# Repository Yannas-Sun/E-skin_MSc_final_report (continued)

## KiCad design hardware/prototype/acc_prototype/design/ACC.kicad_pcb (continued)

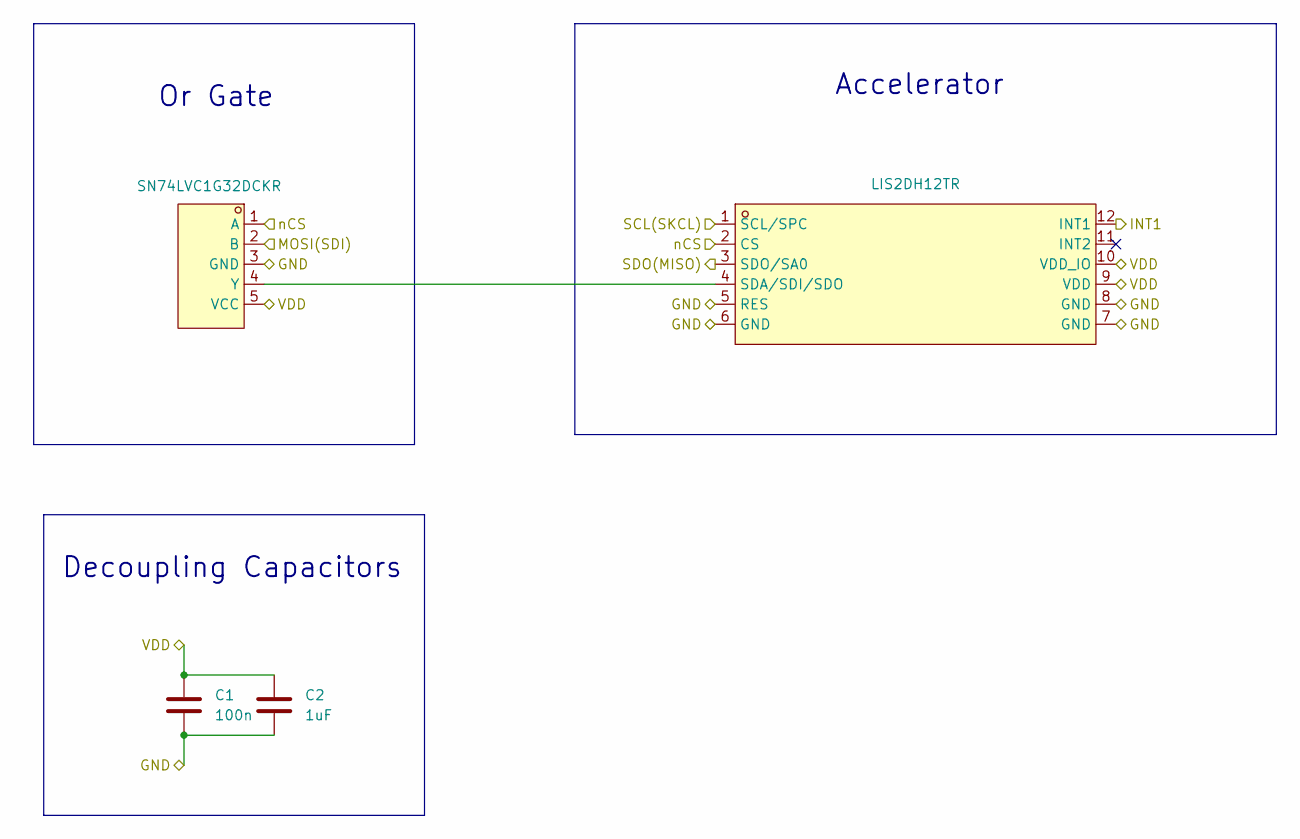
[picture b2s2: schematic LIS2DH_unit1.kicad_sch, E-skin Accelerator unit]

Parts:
C1: 100n; C_0402_1005Metric_Pad0.74x0.62mm_HandSolder; LCSC Part C1525
C2: 1uF; C_0402_1005Metric_Pad0.74x0.62mm_HandSolder; LCSC Part C52923
U1: LIS2DH12TR; LCSC Part C110926
U17: SN74LVC1G32DCKR; LCSC Part C7840

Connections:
/LIS2DH_unit1/INT1: U1.12 (INT1)
GND: C1.2, C2.2, U1.5 (RES), U1.6 (GND), U1.7 (GND), U1.8 (GND), U17.3 (GND); also elsewhere on the board
MISO(SDO): U1.3 (SDO/SA0); also elsewhere on the board
MOSI(SDI): U17.2 (B); also elsewhere on the board
unnamed: U1.4 (SDA/SDI/SDO), U17.4 (Y)
Sclk: U1.1 (SCL/SPC); also elsewhere on the board
VDD: C1.1, C2.1, U1.9 (VDD), U1.10 (VDD_IO), U17.5 (VCC); also elsewhere on the board
nCS_1: U1.2 (CS), U17.1 (A); also elsewhere on the board

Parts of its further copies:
C3, C5, C7, C9, C11, C13, C15, C17: 100n; C_0402_1005Metric_Pad0.74x0.62mm_HandSolder; LCSC Part C1525
C4, C6, C8, C10, C12, C14, C16, C18: 1uF; C_0402_1005Metric_Pad0.74x0.62mm_HandSolder; LCSC Part C52923
U2, U3, U4, U5, U6, U7, U8, U9: LIS2DH12TR; LCSC Part C110926
U18, U19, U20, U21, U22, U23, U24, U25: SN74LVC1G32DCKR; LCSC Part C7840

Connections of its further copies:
/LIS2DH_unit2/INT1: U2.12 (INT1)
/LIS2DH_unit3/INT1: U3.12 (INT1)
/LIS2DH_unit4/INT1: U4.12 (INT1)
/LIS2DH_unit5/INT1: U5.12 (INT1)
/LIS2DH_unit6/INT1: U6.12 (INT1)
/LIS2DH_unit7/INT1: U7.12 (INT1)
/LIS2DH_unit8/INT1: U8.12 (INT1)
/LIS2DH_unit9/INT1: U9.12 (INT1)
GND: C3.2, C4.2, C5.2, C6.2, C7.2, C8.2, C9.2, C10.2, C11.2, C12.2, C13.2, C14.2, C15.2, C16.2, C17.2, C18.2, U2.5 (RES), U2.6 (GND), U2.7 (GND), U2.8 (GND), U3.5 (RES), U3.6 (GND), U3.7 (GND), U3.8 (GND), U4.5 (RES), U4.6 (GND), U4.7 (GND), U4.8 (GND), U5.5 (RES), U5.6 (GND), U5.7 (GND), U5.8 (GND), U6.5 (RES), U6.6 (GND), U6.7 (GND), U6.8 (GND), U7.5 (RES), U7.6 (GND), U7.7 (GND), U7.8 (GND), U8.5 (RES), U8.6 (GND), U8.7 (GND), U8.8 (GND), U9.5 (RES), U9.6 (GND), U9.7 (GND), U9.8 (GND), U18.3 (GND), U19.3 (GND), U20.3 (GND), U21.3 (GND), U22.3 (GND), U23.3 (GND), U24.3 (GND), U25.3 (GND); also elsewhere on the board
MISO(SDO): U2.3 (SDO/SA0), U3.3 (SDO/SA0), U4.3 (SDO/SA0), U5.3 (SDO/SA0), U6.3 (SDO/SA0), U7.3 (SDO/SA0), U8.3 (SDO/SA0), U9.3 (SDO/SA0); also elsewhere on the board
MOSI(SDI): U18.2 (B), U19.2 (B), U20.2 (B), U21.2 (B), U22.2 (B), U23.2 (B), U24.2 (B), U25.2 (B); also elsewhere on the board
unnamed: U2.4 (SDA/SDI/SDO), U18.4 (Y)
unnamed: U3.4 (SDA/SDI/SDO), U19.4 (Y)
unnamed: U4.4 (SDA/SDI/SDO), U20.4 (Y)
unnamed: U5.4 (SDA/SDI/SDO), U21.4 (Y)
unnamed: U6.4 (SDA/SDI/SDO), U22.4 (Y)
unnamed: U7.4 (SDA/SDI/SDO), U23.4 (Y)
unnamed: U8.4 (SDA/SDI/SDO), U24.4 (Y)
unnamed: U9.4 (SDA/SDI/SDO), U25.4 (Y)
Sclk: U2.1 (SCL/SPC), U3.1 (SCL/SPC), U4.1 (SCL/SPC), U5.1 (SCL/SPC), U6.1 (SCL/SPC), U7.1 (SCL/SPC), U8.1 (SCL/SPC), U9.1 (SCL/SPC); also elsewhere on the board
VDD: C3.1, C4.1, C5.1, C6.1, C7.1, C8.1, C9.1, C10.1, C11.1, C12.1, C13.1, C14.1, C15.1, C16.1, C17.1, C18.1, U2.9 (VDD), U2.10 (VDD_IO), U3.9 (VDD), U3.10 (VDD_IO), U4.9 (VDD), U4.10 (VDD_IO), U5.9 (VDD), U5.10 (VDD_IO), U6.9 (VDD), U6.10 (VDD_IO), U7.9 (VDD), U7.10 (VDD_IO), U8.9 (VDD), U8.10 (VDD_IO), U9.9 (VDD), U9.10 (VDD_IO), U18.5 (VCC), U19.5 (VCC), U20.5 (VCC), U21.5 (VCC), U22.5 (VCC), U23.5 (VCC), U24.5 (VCC), U25.5 (VCC); also elsewhere on the board
nCS_2: U2.2 (CS), U18.1 (A); also elsewhere on the board
nCS_3: U3.2 (CS), U19.1 (A); also elsewhere on the board
nCS_4: U4.2 (CS), U20.1 (A); also elsewhere on the board
nCS_5: U5.2 (CS), U21.1 (A); also elsewhere on the board
nCS_6: U6.2 (CS), U22.1 (A); also elsewhere on the board
nCS_7: U7.2 (CS), U23.1 (A); also elsewhere on the board
nCS_8: U8.2 (CS), U24.1 (A); also elsewhere on the board
nCS_9: U9.2 (CS), U25.1 (A); also elsewhere on the board

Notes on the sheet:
Decoupling Capacitors
Accelerator
Or Gate

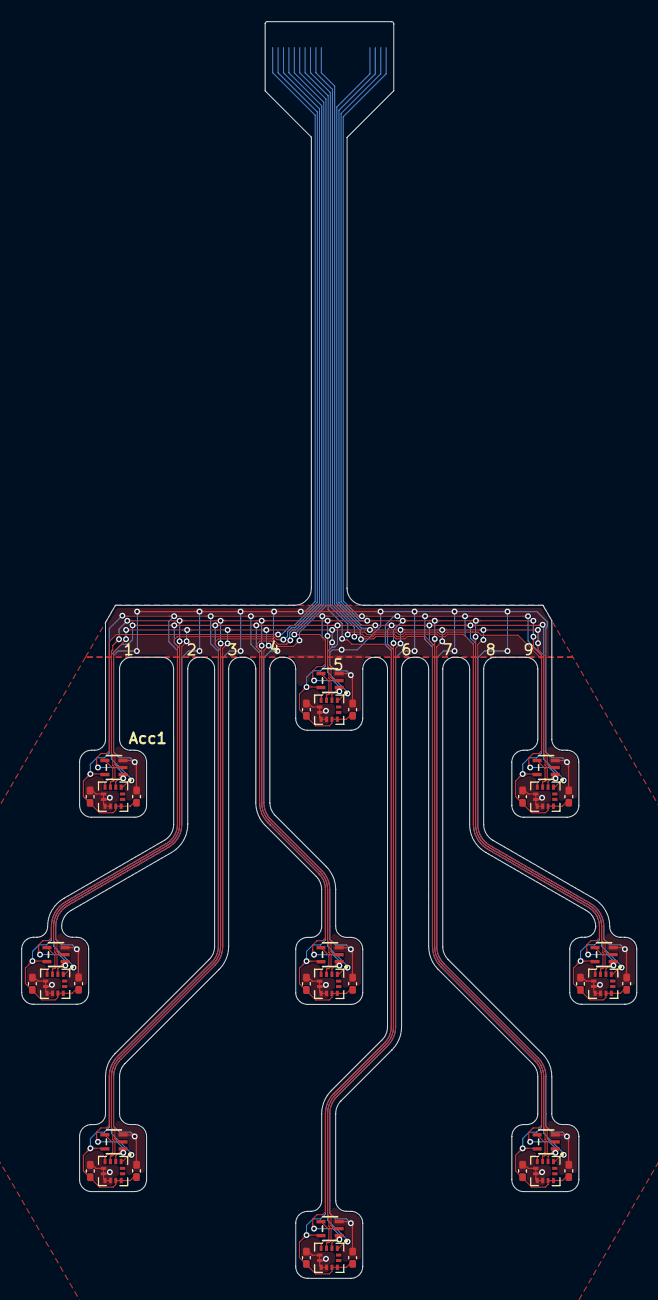
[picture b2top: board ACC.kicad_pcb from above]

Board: 2 copper layers, 56.9 x 116.3 mm, 37 parts (1 on the bottom side), 23 nets.

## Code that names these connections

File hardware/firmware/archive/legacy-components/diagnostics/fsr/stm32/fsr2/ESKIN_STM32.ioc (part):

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Mcu.Name=STM32G474C(B-C-E)Tx
Mcu.Package=LQFP48
Mcu.UserName=STM32G474CETx
PA0.GPIOParameters=GPIO_Label
PA0.GPIO_Label=MUX S0
PA0.Signal=GPIO_Output
PA1.GPIOParameters=GPIO_Label
PA1.GPIO_Label=MUX S1
PA1.Signal=GPIO_Output
PA13.Mode=Serial_Wire
PA13.Signal=SYS_JTMS-SWDIO
PA14.Mode=Serial_Wire
PA14.Signal=SYS_JTCK-SWCLK
PA15.Mode=NSS_Signal_Hard_Input
PA15.Signal=SPI3_NSS
PA2.GPIOParameters=GPIO_Label
PA2.GPIO_Label=MUX S2
PA2.Signal=GPIO_Output
PA3.GPIOParameters=GPIO_Label
PA3.GPIO_Label=MUX S3
PA3.Signal=GPIO_Output
PA4.GPIOParameters=GPIO_Label,GPIO_OutputState
PA4.GPIO_Label=MUX EN1
PA4.GPIO_OutputState=GPIO_PIN_SET
PA4.Signal=GPIO_Output
PA5.Mode=Full_Duplex_Master
PA5.Signal=SPI1_SCK
PA6.Mode=Full_Duplex_Master
PA6.Signal=SPI1_MISO
PA7.Mode=Full_Duplex_Master
PA7.Signal=SPI1_MOSI
PB0.GPIOParameters=GPIO_Label,GPIO_OutputState
PB0.GPIO_Label=ADC_CS1
PB0.GPIO_OutputState=GPIO_PIN_SET
PB0.Signal=GPIO_Output
PB1.GPIOParameters=GPIO_Label,GPIO_OutputState
PB1.GPIO_Label=ADC_CS2
PB1.GPIO_OutputState=GPIO_PIN_SET
PB1.Signal=GPIO_Output
PB2.GPIOParameters=GPIO_Label,GPIO_OutputState
PB2.GPIO_Label=MUX EN2
PB2.GPIO_OutputState=GPIO_PIN_SET
PB2.Signal=GPIO_Output
PB10.GPIOParameters=GPIO_Label
PB10.GPIO_Label=ADC_EOC1
PB10.Signal=GPIO_Input
PB11.GPIOParameters=GPIO_Label
PB11.GPIO_Label=ADC_EOC2
PB11.Signal=GPIO_Input
PB3.Mode=Full_Duplex_Slave
PB3.Signal=SPI3_SCK
PB4.Mode=Full_Duplex_Slave
PB4.Signal=SPI3_MISO
PB5.Mode=Full_Duplex_Slave
PB5.Signal=SPI3_MOSI
PB8-BOOT0.GPIOParameters=GPIO_Label
PB8-BOOT0.GPIO_Label=HOST_IRQ
PB8-BOOT0.Signal=GPIO_Output
PB9.GPIOParameters=GPIO_Label
PB9.GPIO_Label=HOST_SYNC
PB9.Signal=GPIO_Input
RCC.HSE_VALUE=8000000
RCC.SYSCLKFreq_VALUE=16000000
board=custom
